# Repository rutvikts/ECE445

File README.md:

# ECE 445
UIUC ECE 445 - Senior Design Project Repository

# Project Details
## Oxygen Delivery Robot

Team Members:
- Rutvik Sayankar (rutviks2@illinois.edu)
- Aidan Dunican (dunican2@illinois.edu)
- Nazar Kalyniouk (nazark2@illinois.edu)

## Problem

Children's interstitial and diffuse lung disease (ChILD) is a collection of diseases or disorders. These diseases cause a thickening of the interstitium (the tissue that extends throughout the lungs) due to scarring, inflammation, or fluid buildup. This eventually affects a patient’s ability to breathe and distribute enough oxygen to the blood.

Numerous children experience the impact of this situation, requiring supplemental oxygen for their daily activities. It hampers the mobility and freedom of young infants, diminishing their growth and confidence. Moreover, parents face an increased burden, not only caring for their child but also being directly involved in managing the oxygen tank as their child moves around.

## Solution

Mobile oxygen delivery is a mostly untapped market for users both elderly and young. This project details a prototype design for a mobile oxygen delivery robot. We utilize a three-wheeled omnidirectional drivetrain, ultra-wideband triangulation, computer vision, and a simple Roomba-style bumper system. We remove ourselves from the context of dealing with oxygen-related tubing as swivel solutions already exist and focus on the issue of creating a robot that can autonomously and efficiently move an oxygen tank around in an indoor space.

### Final Robot Design

### Final Robot Wiring (Underside)

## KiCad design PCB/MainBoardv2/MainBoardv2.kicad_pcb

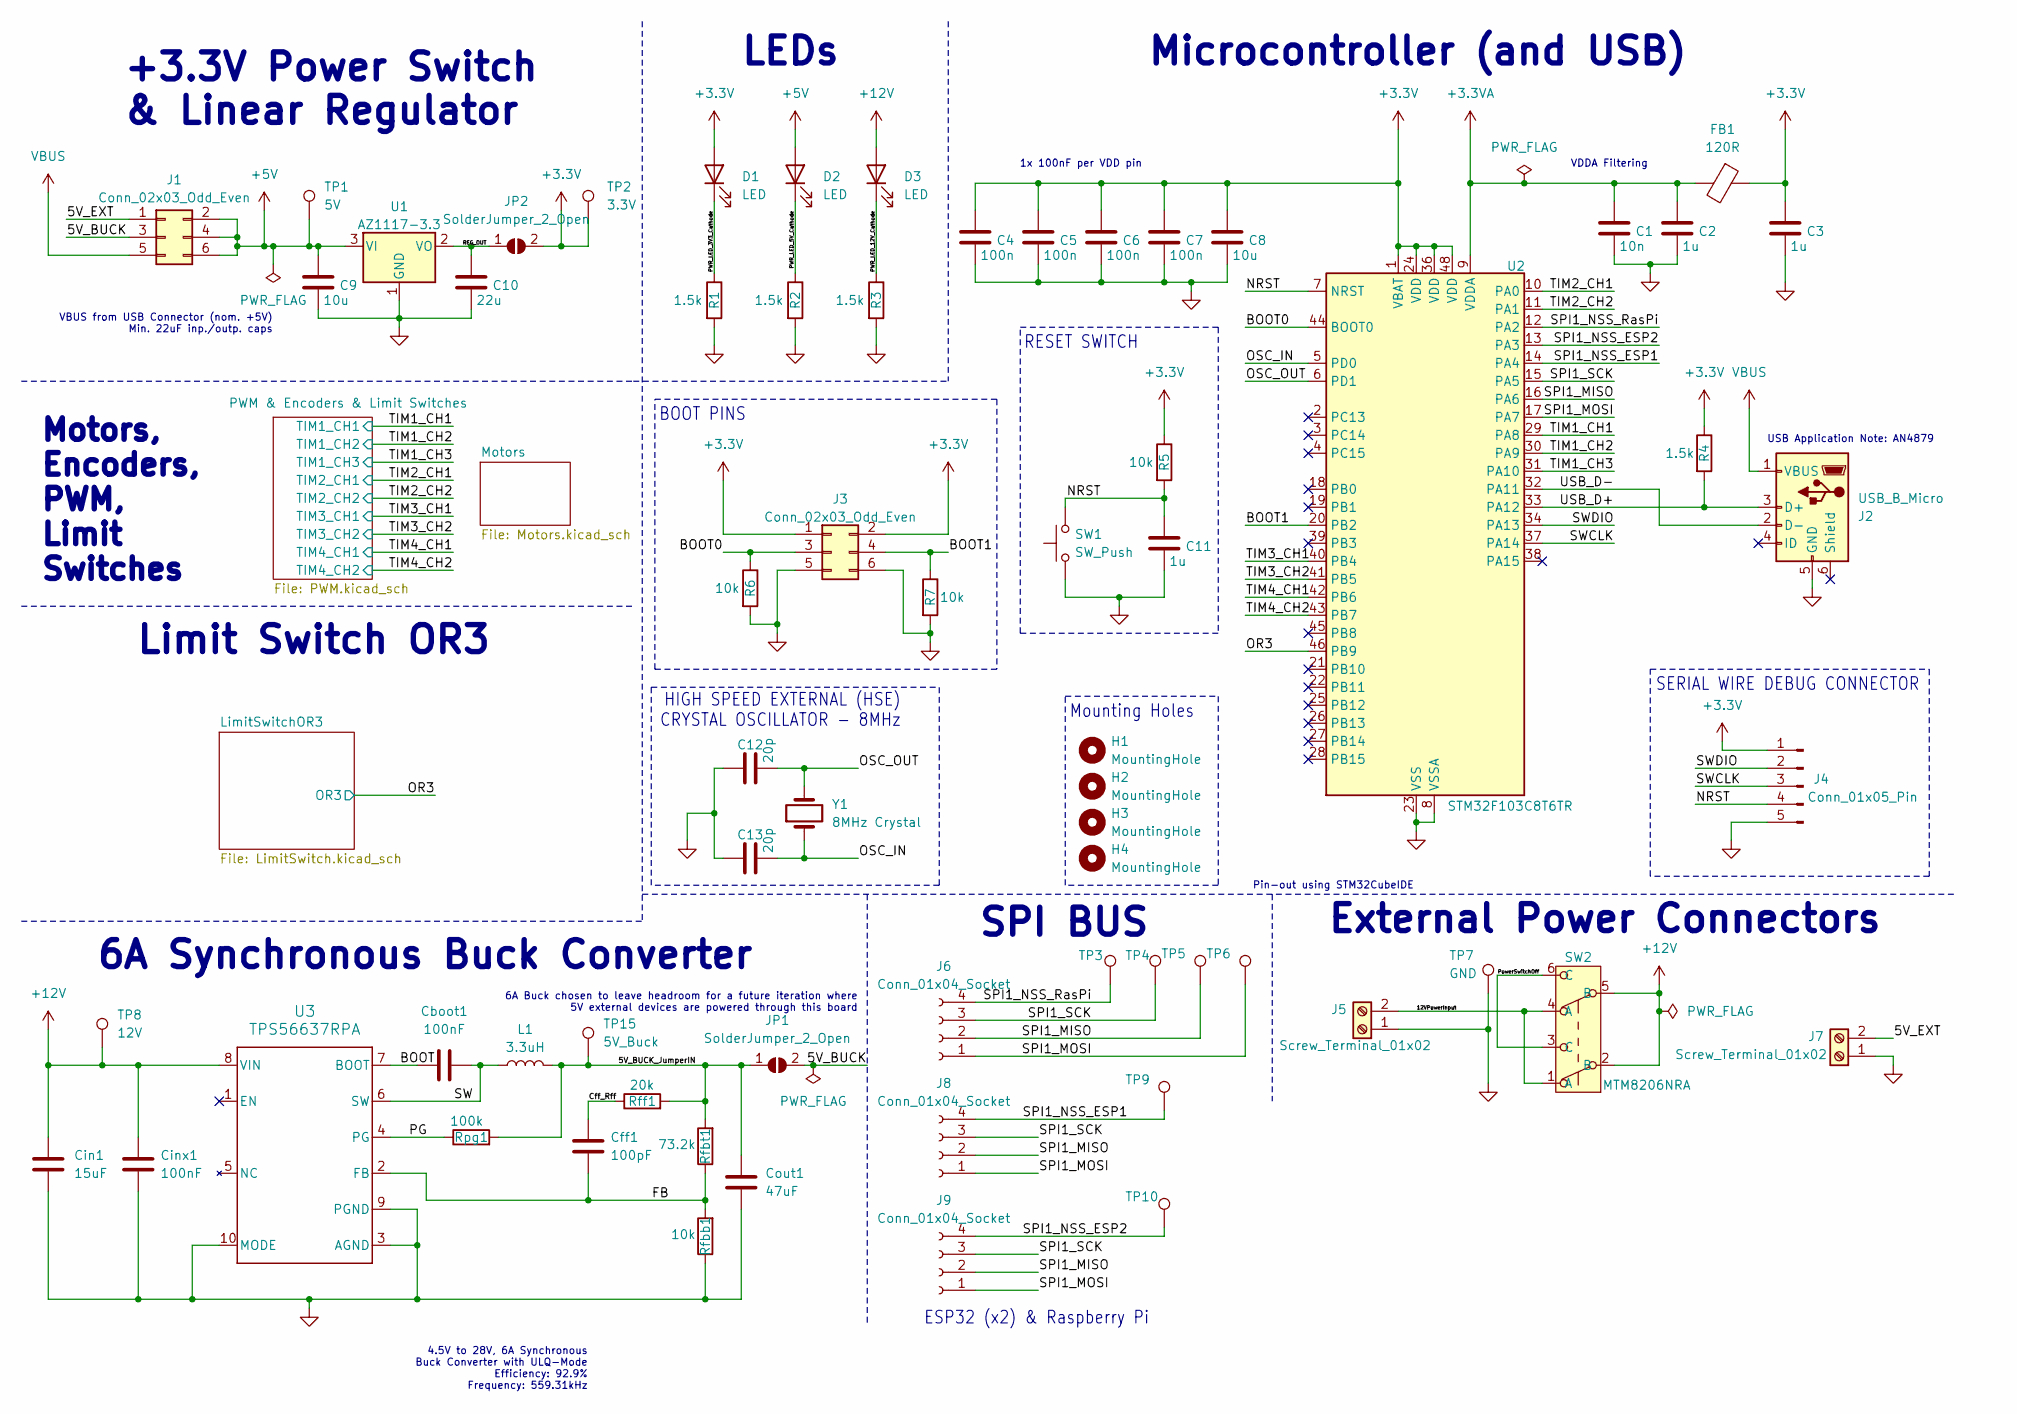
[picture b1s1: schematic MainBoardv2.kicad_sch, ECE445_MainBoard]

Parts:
C1: 10n; C_0603_1608Metric
C2, C3, C11: 1u; C_0603_1608Metric
C4, C5, C6, C7: 100n; C_0603_1608Metric
C8, C9: 10u; C_0603_1608Metric
C10: 22u; C_0805_2012Metric
C12, C13: 20p; C_0603_1608Metric
Cboot1: 100nF; C_0805_2012Metric
Cff1: 100pF; C_0805_2012Metric
Cin1: 15uF; C_0805_2012Metric
Cinx1: 100nF; C_0805_2012Metric
Cout1: 47uF; C_1210_3225Metric
D1, D2, D3: LED; LED_0603_1608Metric
FB1: 120R; L_0603_1608Metric
H1, H2, H3, H4: MountingHole; MountingHole_5mm
J1, J3: Conn_02x03_Odd_Even; PinHeader_2x03_P2.54mm_Vertical
J2: USB_B_Micro; AMPHENOL_10118192-0002LF
J4: Conn_01x05_Pin; PinSocket_1x05_P2.54mm_Vertical
J5, J7: Screw_Terminal_01x02; PHOENIX_1017521
J6, J8, J9: Conn_01x04_Socket; PinHeader_1x04_P2.54mm_Horizontal
JP1, JP2: SolderJumper_2_Open; SolderJumper-2_P1.3mm_Open_TrianglePad1.0x1.5mm
L1: 3.3uH; IHLP3232DZER3R3M01
R1, R2, R3, R4: 1.5k; R_0603_1608Metric
R5, R6, R7: 10k; R_0603_1608Metric
Rfbb1: 10k; R_0805_2012Metric
Rfbt1: 73.2k; R_0805_2012Metric
Rff1: 20k; R_0805_2012Metric
Rpg1: 100k; R_0805_2012Metric
SW1: SW_Push; SW_PUSH_6mm_H7.3mm
SW2: Toggle; MTM8206NRA
TP1: 5V; TestPoint_Keystone_5000-5004_Miniature
TP2: 3.3V; TestPoint_Keystone_5000-5004_Miniature
TP3, TP4, TP5, TP6, TP9, TP10: Orange; TestPoint_Keystone_5000-5004_Miniature
TP7: GND; TestPoint_Keystone_5000-5004_Miniature
TP8: 12V; TestPoint_Keystone_5000-5004_Miniature
TP15: 5V_Buck; TestPoint_Keystone_5000-5004_Miniature
U1: AZ1117-3.3; TO-252-2
U2: STM32F103C8T6TR; LQFP-48_7x7mm_P0.5mm
U3: TPS56637RPA; RPA0010A
Y1: 8MHz Crystal; Crystal_HC49-U_Vertical

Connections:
+3.3V: C3.1, C4.1, C5.1, C6.1, C7.1, C8.1, D1.2 (A), FB1.1, J3.1, J3.2, J4.1, JP2.2 (B), R4.1, R5.1, TP2.1, U2.1 (VBAT), U2.24 (VDD), U2.36 (VDD), U2.48 (VDD); also elsewhere on the board
+3.3VA: C1.1, C2.1, FB1.2, U2.9 (VDDA)
+5V: C9.1, D2.2 (A), J1.2, J1.4, J1.6, TP1.1, U1.3 (VI); also elsewhere on the board
+12V: Cin1.1, Cinx1.1, D3.2 (A), SW2.2 (B), SW2.5 (B), TP8.1, U3.8 (VIN); also elsewhere on the board
/5V_BUCK: J1.3, JP1.2 (B)
/5V_BUCK_JumperIN: Cout1.1, JP1.1 (A), L1.2, Rfbt1.2, Rff1.2, Rpg1.2, TP15.1
/5V_EXT: J1.1, J7.2
/12VPowerInput: J5.2, SW2.1 (A), SW2.4 (A)
/BOOT: Cboot1.1, U3.7 (BOOT)
/BOOT0: J3.3, R6.1, U2.44 (BOOT0)
/BOOT1: J3.4, R7.1, U2.20 (PB2)
/Cff_Rff: Cff1.1, Rff1.1
/FB: Cff1.2, Rfbb1.2, Rfbt1.1, U3.2 (FB)
/NRST: C11.1, J4.4, R5.2, SW1.2, U2.7 (NRST)
/OR3: U2.46 (PB9); also elsewhere on the board
/OSC_IN: C13.2, U2.5 (PD0), Y1.1
/OSC_OUT: C12.2, U2.6 (PD1), Y1.2
/PG: Rpg1.1, U3.4 (PG)
/PWR_LED_3V3_Cathode: D1.1 (K), R1.1
/PWR_LED_5V_Cathode: D2.1 (K), R2.1
/PWR_LED_12V_Cathode: D3.1 (K), R3.1
/PowerSwitchOff: SW2.3 (C), SW2.6 (C)
/REG_OUT: C10.1, JP2.1 (A), U1.2 (VO)
/SPI1_MISO: J6.2, J8.2, J9.2, TP5.1, U2.16 (PA6)
/SPI1_MOSI: J6.1, J8.1, J9.1, TP6.1, U2.17 (PA7)
/SPI1_NSS_ESP1: J8.4, TP9.1, U2.14 (PA4)
/SPI1_NSS_ESP2: J9.4, TP10.1, U2.13 (PA3)
/SPI1_NSS_RasPi: J6.4, TP3.1, U2.12 (PA2)
/SPI1_SCK: J6.3, J8.3, J9.3, TP4.1, U2.15 (PA5)
/SW: Cboot1.2, L1.1, U3.6 (SW)
/SWCLK: J4.3, U2.37 (PA14)
/SWDIO: J4.2, U2.34 (PA13)
/TIM1_CH1: U2.29 (PA8); also elsewhere on the board
/TIM1_CH2: U2.30 (PA9); also elsewhere on the board
/TIM1_CH3: U2.31 (PA10); also elsewhere on the board
/TIM2_CH1: U2.10 (PA0); also elsewhere on the board
/TIM2_CH2: U2.11 (PA1); also elsewhere on the board
/TIM3_CH1: U2.40 (PB4); also elsewhere on the board
/TIM3_CH2: U2.41 (PB5); also elsewhere on the board
/TIM4_CH1: U2.42 (PB6); also elsewhere on the board
/TIM4_CH2: U2.43 (PB7); also elsewhere on the board
/USB_D+: J2.3 (D+), R4.2, U2.33 (PA12)
/USB_D-: J2.2 (D-), U2.32 (PA11)
GND: C1.2, C2.2, C3.2, C4.2, C5.2, C6.2, C7.2, C8.2, C9.2, C10.2, C11.2, C12.1, C13.1, Cin1.2, Cinx1.2, Cout1.2, J2.5 (GND), J3.5, J3.6, J4.5, J5.1, J7.1, R1.2, R2.2, R3.2, R6.2, R7.2, Rfbb1.1, SW1.1, TP7.1, U1.1 (GND), U2.8 (VSSA), U2.23 (VSS), U2.35 (VSS), U2.47 (VSS), U3.3 (AGND), U3.9 (PGND), U3.10 (MODE); also elsewhere on the board
VBUS: J1.5, J2.1 (VBUS)

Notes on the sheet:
RESET SWITCH
Limit Switch OR3
SERIAL WIRE DEBUG CONNECTOR
BOOT PINS
VDDA Filtering
Microcontroller (and USB)
1x 100nF per VDD pin
External Power Connectors
LEDs
6A Buck chosen to leave headroom for a future iteration where 5V external devices are powered through this board
Pin-out using STM32CubeIDE
VBUS from USB Connector (nom. +5V) Min. 22uF inp./outp. caps
6A Synchronous Buck Converter
Motors, Encoders, PWM, Limit Switches
Mounting Holes
ESP32 (x2) & Raspberry Pi
USB Application Note: AN4879
4.5V to 28V, 6A Synchronous Buck Converter with ULQ-Mode Efficiency: 92.9% Frequency: 559.31kHz
SPI BUS
HIGH SPEED EXTERNAL (HSE) CRYSTAL OSCILLATOR - 8MHz
+3.3V Power Switch & Linear Regulator

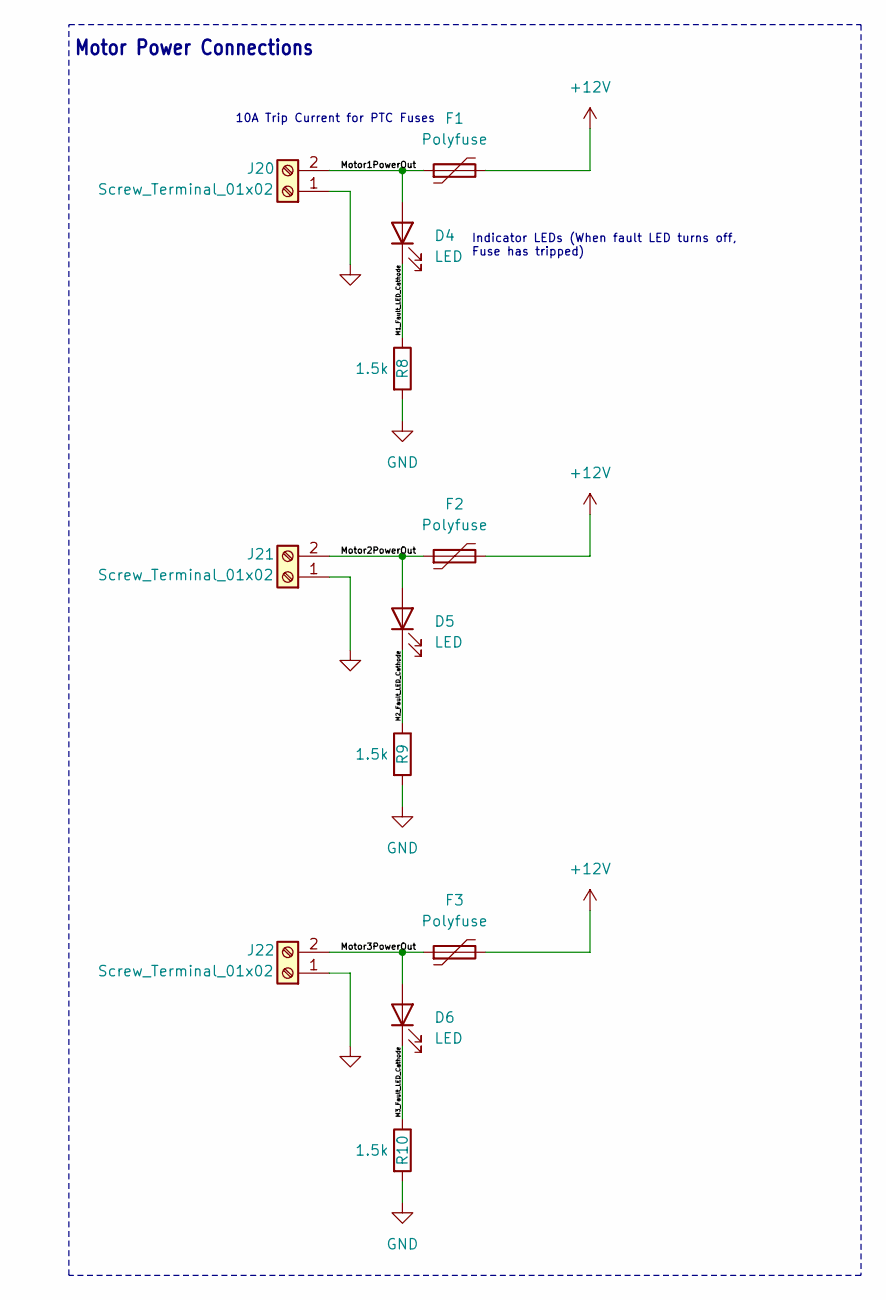
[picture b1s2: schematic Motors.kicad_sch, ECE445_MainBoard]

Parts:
D4, D5, D6: LED; LED_0603_1608Metric
F1, F2, F3: Polyfuse; Fuse_2920_7451Metric
J20, J21, J22: Screw_Terminal_01x02; PHOENIX_1017521
R8, R9, R10: 1.5k; R_0603_1608Metric

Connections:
+12V: F1.2, F2.2, F3.2; also elsewhere on the board
/Motors/M1_Fault_LED_Cathode: D4.1 (K), R8.1
/Motors/M2_Fault_LED_Cathode: D5.1 (K), R9.1
/Motors/M3_Fault_LED_Cathode: D6.1 (K), R10.1
/Motors/Motor1PowerOut: D4.2 (A), F1.1, J20.2
/Motors/Motor2PowerOut: D5.2 (A), F2.1, J21.2
/Motors/Motor3PowerOut: D6.2 (A), F3.1, J22.2
GND: J20.1, J21.1, J22.1, R8.2, R9.2, R10.2; also elsewhere on the board

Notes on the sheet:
Indicator LEDs (When fault LED turns off, Fuse has tripped)
Motor Power Connections
10A Trip Current for PTC Fuses

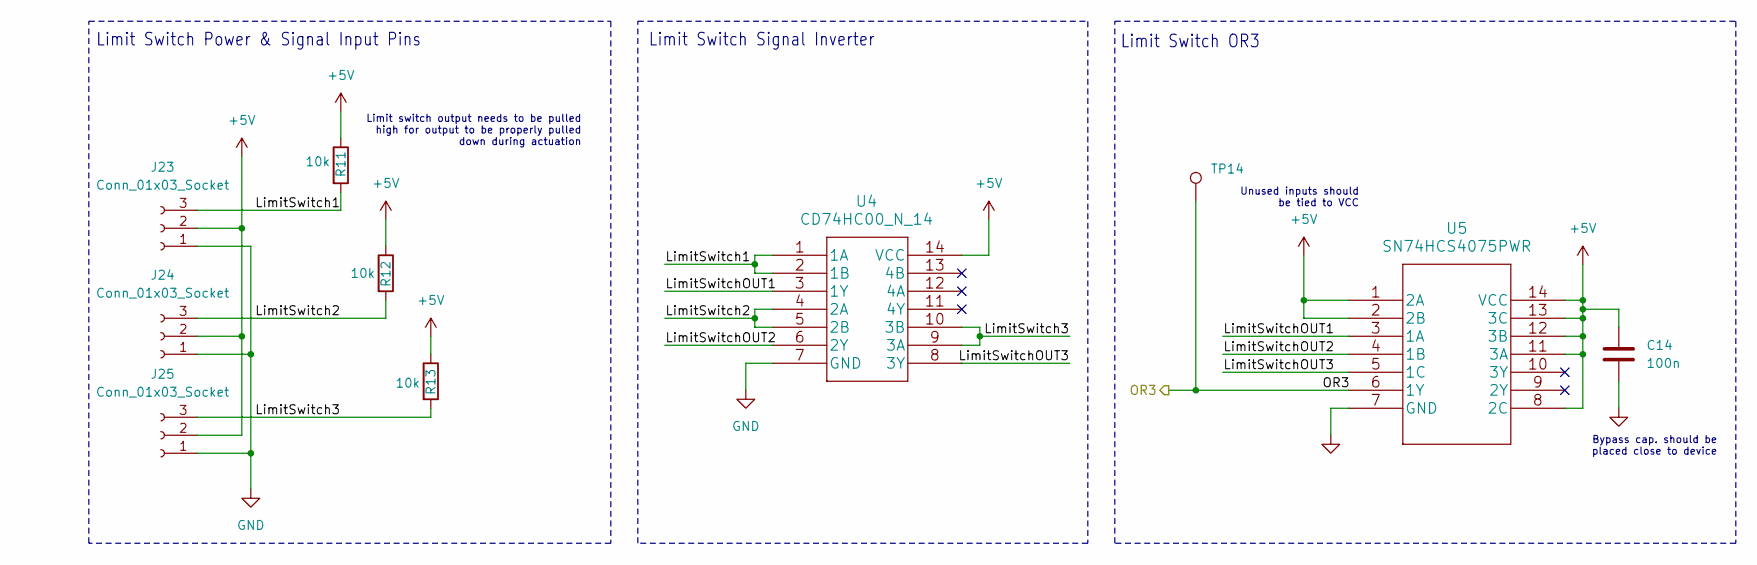
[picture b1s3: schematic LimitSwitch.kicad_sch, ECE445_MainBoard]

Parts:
C14: 100n; C_0603_1608Metric
J23, J24, J25: Conn_01x03_Socket; PinHeader_1x03_P2.54mm_Horizontal
R11, R12, R13: 10k; R_Axial_DIN0207_L6.3mm_D2.5mm_P7.62mm_Horizontal
TP14: White; TestPoint_Keystone_5000-5004_Miniature
U4: CD74HC00_N_14; DIP-14_W7.62mm_LongPads
U5: SN74HCS4075PWR

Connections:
+5V: C14.1, J23.2, J24.2, J25.2, R11.1, R12.1, R13.1, U4.14 (VCC), U5.1 (2A), U5.2 (2B), U5.8 (2C), U5.11 (3A), U5.12 (3B), U5.13 (3C), U5.14 (VCC); also elsewhere on the board
/LimitSwitchOR3/LimitSwitch1: J23.3, R11.2, U4.1 (1A), U4.2 (1B)
/LimitSwitchOR3/LimitSwitch2: J24.3, R12.2, U4.4 (2A), U4.5 (2B)
/LimitSwitchOR3/LimitSwitch3: J25.3, R13.2, U4.9 (3A), U4.10 (3B)
/LimitSwitchOR3/LimitSwitchOUT1: U4.3 (1Y), U5.3 (1A)
/LimitSwitchOR3/LimitSwitchOUT2: U4.6 (2Y), U5.4 (1B)
/LimitSwitchOR3/LimitSwitchOUT3: U4.8 (3Y), U5.5 (1C)
/OR3: TP14.1, U5.6 (1Y); also elsewhere on the board
GND: C14.2, J23.1, J24.1, J25.1, U4.7 (GND), U5.7 (GND); also elsewhere on the board

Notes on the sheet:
Bypass cap. should be placed close to device
Limit Switch OR3
Limit Switch Signal Inverter
Unused inputs should be tied to VCC
Limit switch output needs to be pulled high for output to be properly pulled down during actuation
Limit Switch Power & Signal Input Pins

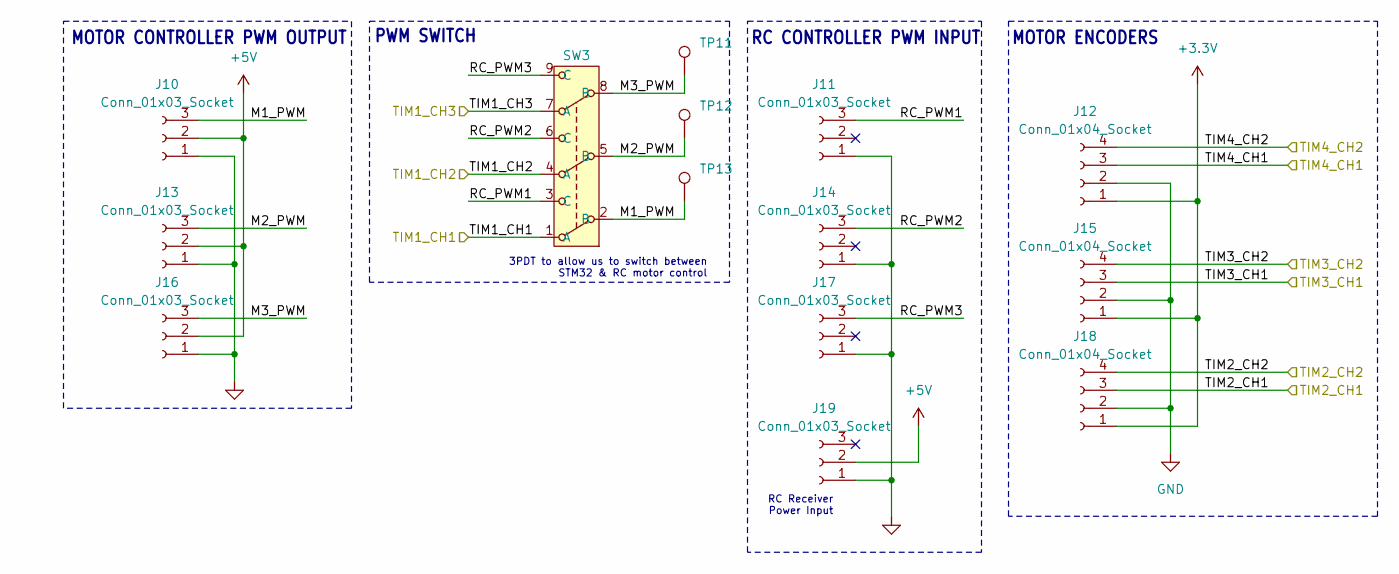
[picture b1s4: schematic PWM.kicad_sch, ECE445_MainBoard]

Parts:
J10, J13, J16: Conn_01x03_Socket; PinHeader_1x03_P2.54mm_Horizontal
J11, J14, J17, J19: Conn_01x03_Socket; PinHeader_1x03_P2.54mm_Vertical
J12, J15, J18: Conn_01x04_Socket; JST_PH_B4B-PH-K_1x04_P2.00mm_Vertical
SW3: Slide; SW_GF-161-0005
TP11, TP12, TP13: White; TestPoint_Keystone_5000-5004_Miniature

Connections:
+3.3V: J12.1, J15.1, J18.1; also elsewhere on the board
+5V: J10.2, J13.2, J16.2, J19.2; also elsewhere on the board
/PWM & Encoders & Limit Switches/M1_PWM: J10.3, SW3.2 (B), TP13.1
/PWM & Encoders & Limit Switches/M2_PWM: J13.3, SW3.5 (B), TP12.1
/PWM & Encoders & Limit Switches/M3_PWM: J16.3, SW3.8 (B), TP11.1
/PWM & Encoders & Limit Switches/RC_PWM1: J11.3, SW3.3 (C)
/PWM & Encoders & Limit Switches/RC_PWM2: J14.3, SW3.6 (C)
/PWM & Encoders & Limit Switches/RC_PWM3: J17.3, SW3.9 (C)
/TIM1_CH1: SW3.1 (A); also elsewhere on the board
/TIM1_CH2: SW3.4 (A); also elsewhere on the board
/TIM1_CH3: SW3.7 (A); also elsewhere on the board
/TIM2_CH1: J18.3; also elsewhere on the board
/TIM2_CH2: J18.4; also elsewhere on the board
/TIM3_CH1: J15.3; also elsewhere on the board
/TIM3_CH2: J15.4; also elsewhere on the board
/TIM4_CH1: J12.3; also elsewhere on the board
/TIM4_CH2: J12.4; also elsewhere on the board
GND: J10.1, J11.1, J12.2, J13.1, J14.1, J15.2, J16.1, J17.1, J18.2, J19.1; also elsewhere on the board

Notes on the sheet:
MOTOR ENCODERS
MOTOR CONTROLLER PWM OUTPUT
PWM SWITCH
RC Receiver Power Input
3PDT to allow us to switch between STM32 & RC motor control
RC CONTROLLER PWM INPUT

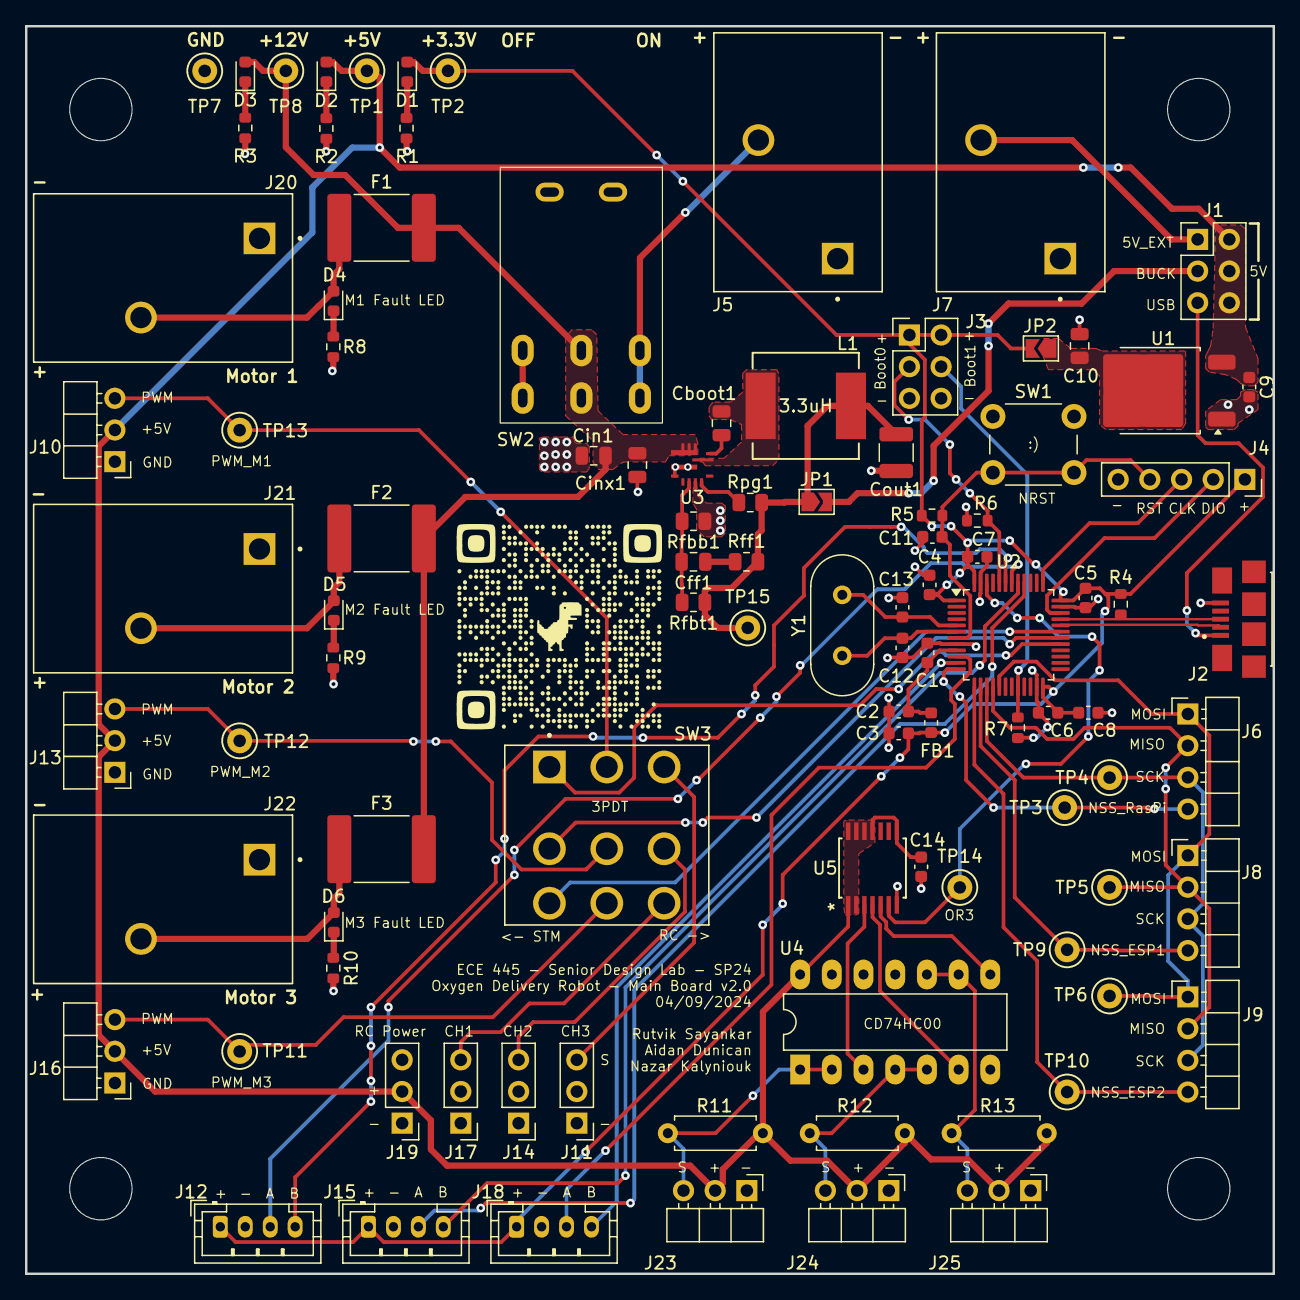
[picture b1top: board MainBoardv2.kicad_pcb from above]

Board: 2 copper layers, 100.0 x 100.0 mm, 102 parts (0 on the bottom side), 63 nets.

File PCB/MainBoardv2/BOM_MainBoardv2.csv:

Reference,Value,Datasheet,Footprint,Qty,DNP
C1,10n,https://www.digikey.com/en/products/detail/kemet/C0603C103K4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,Capacitor_SMD:C_0603_1608Metric,1,
"C2,C3,C11",1u,https://www.digikey.com/en/products/detail/yageo/CC0603KRX7R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,Capacitor_SMD:C_0603_1608Metric,3,
"C4,C5,C6,C7,C13",100n,https://www.digikey.com/en/products/detail/yageo/CC0603KRX7R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,Capacitor_SMD:C_0603_1608Metric,5,
"C8,C9",10u,https://www.digikey.com/en/products/detail/samsung-electro-m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,Capacitor_SMD:C_0603_1608Metric,2,
C10,22u,https://www.digikey.com/en/products/detail/samsung-electro-m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,Capacitor_SMD:C_0805_2012Metric,1,
"C12,C14",20p,https://www.digikey.com/en/products/detail/kemet/C0603C200G8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,Capacitor_SMD:C_0603_1608Metric,2,
Cboot?,100nF,https://www.digikey.com/en/products/detail/kyocera-avx/KGM21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,Capacitor_SMD:C_0805_2012Metric,1,
Cff?,100pF,https://www.digikey.com/en/products/detail/kemet/C0805C101K3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,Capacitor_SMD:C_0805_2012Metric,1,
Cin?,15uF,https://www.digikey.com/en/products/detail/tdk-corporation/C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,Capacitor_SMD:C_0805_2012Metric,1,
Cinx?,100nF,https://www.digikey.com/en/products/detail/knowles-syfer/080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,Capacitor_SMD:C_0805_2012Metric,1,
Cout?,47uF,https://www.digikey.com/en/products/detail/murata-electronic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,Capacitor_SMD:C_1210_3225Metric,1,
"D1,D2,D3,D4,D5,D6,D7,D8,D9",LED,https://www.digikey.com/en/products/detail/w%C3%BCrth-elektr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,LED_SMD:LED_0603_1608Metric,9,
"F1,F2,F3",Polyfuse,https://www.digikey.com/en/products/detail/yageo/SMD2920B500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,Fuse:Fuse_2920_7451Metric,3,
FB1,120R,https://www.digikey.com/en/products/detail/murata-electronic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,Inductor_SMD:L_0603_1608Metric,1,
"H1,H2,H3,H4",MountingHole,~,MountingHole:MountingHole_5mm,4,
"J1,J3",Conn_02x03_Odd_Even,~,Connector_PinSocket_2.54mm:PinSocket_2x03_P2.54mm_Vertical,2,
J2,USB_B_Micro,https://www.digikey.com/en/products/detail/amphenol-cs-fci/1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,CustomFootprints:AMPHENOL_10118192-0002LF,1,
J4,Conn_01x05_Pin,~,Connector_PinSocket_2.54mm:PinSocket_1x05_P2.54mm_Vertical,1,
"J5,J11,J12,J14,J15,J17,J18,J20",Conn_01x03_Socket,~,Connector_PinHeader_2.54mm:PinHeader_1x03_P2.54mm_Vertical,8,
"J6,J8,J21,J22,J23",Screw_Terminal_01x02,https://www.digikey.com/en/products/detail/phoenix-contact/1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,CustomFootprints:1985195,5,
"J7,J9,J10",Conn_01x04_Socket,~,Connector_PinHeader_2.54mm:PinHeader_1x04_P2.54mm_Vertical,3,
"J13,J16,J19",Conn_01x04_Socket,https://www.digikey.com/en/products/detail/jst-sales-america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,Connector_JST:JST_PH_B4B-PH-K_1x04_P2.00mm_Vertical,3,
L1,3.3uH,https://www.digikey.com/en/products/detail/vishay-dale/IHLP3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,CustomFootprints:IHLP3232DZER3R3M01,1,
"R1,R2,R3,R4,R8,R9,R10,R11,R12,R13",1.5k,https://www.digikey.com/en/products/detail/yageo/RC0603JR-07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,Resistor_SMD:R_0603_1608Metric,10,
"R5,R6,R7",10k,https://www.digikey.com/en/products/detail/stackpole-electro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,Resistor_SMD:R_0603_1608Metric,3,
Rfbb?,10k,https://www.digikey.com/en/products/detail/vishay-dale/CRCW0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,Resistor_SMD:R_0805_2012Metric,1,
Rfbt?,73.2k,https://www.digikey.com/en/products/detail/panasonic-electro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,Resistor_SMD:R_0805_2012Metric,1,
Rff?,20k,https://www.digikey.com/en/products/detail/vishay-dale/CRCW0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,Resistor_SMD:R_0805_2012Metric,1,
Rpg?,100k,https://www.digikey.com/en/products/detail/vishay-dale/CRCW0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,Resistor_SMD:R_0805_2012Metric,1,
SW1,SW_Push,https://www.digikey.com/en/products/detail/omron-electronics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,Button_Switch_SMD:SW_SPST_B3S-1000,1,
SW2,Toggle,https://mm.digikey.com/Volume0/opasdata/d220001/medias/docus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,CustomFootprints:MTM8206NRA,1,
SW3,Slide,https://www.digikey.com/en/products/detail/cw-industries/GF-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,CustomFootprints:SW_GF-161-0005,1,
TP1,5V,https://www.digikey.com/en/products/detail/keystone-electron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,TestPoint:TestPoint_Keystone_5000-5004_Miniature,1,
TP2,3.3V,https://www.digikey.com/en/products/detail/keystone-electron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,TestPoint:TestPoint_Keystone_5000-5004_Miniature,1,
"TP3,TP11,TP12,TP13",White,https://www.digikey.com/en/products/detail/keystone-electron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,TestPoint:TestPoint_Keystone_5000-5004_Miniature,4,
"TP4,TP5,TP6,TP7,TP9,TP10",Orange,https://www.digikey.com/en/products/detail/keystone-electron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,TestPoint:TestPoint_Keystone_5000-5004_Miniature,6,
TP8,12V,https://www.digikey.com/en/products/detail/keystone-electron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,TestPoint:TestPoint_Keystone_5000-5004_Miniature,1,
TP14,GND,https://www.digikey.com/en/products/detail/keystone-electron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,TestPoint:TestPoint_Keystone_5000-5004_Miniature,1,
U1,AZ1117-3.3,https://www.digikey.com/en/products/detail/diodes-incorporat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,Package_TO_SOT_SMD:TO-252-2,1,
U2,STM32F103C8T6TR,https://www.st.com/resource/en/datasheet/stm32f103c8.pdf,Package_QFP:LQFP-48_7x7mm_P0.5mm,1,
U3,SN74HCS4075PWR,https://www.digikey.com/en/products/detail/texas-instruments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,CustomFootprints:SN74HCS4075PWR,1,
U4,TPS56637RPA,https://www.digikey.com/en/products/detail/texas-instruments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,CustomFootprints:RPA0010A,1,
Y1,8MHz Crystal,https://www.digikey.com/en/products/detail/ecs-inc/ECS-080-2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,Crystal:Crystal_HC49-U_Vertical,1,

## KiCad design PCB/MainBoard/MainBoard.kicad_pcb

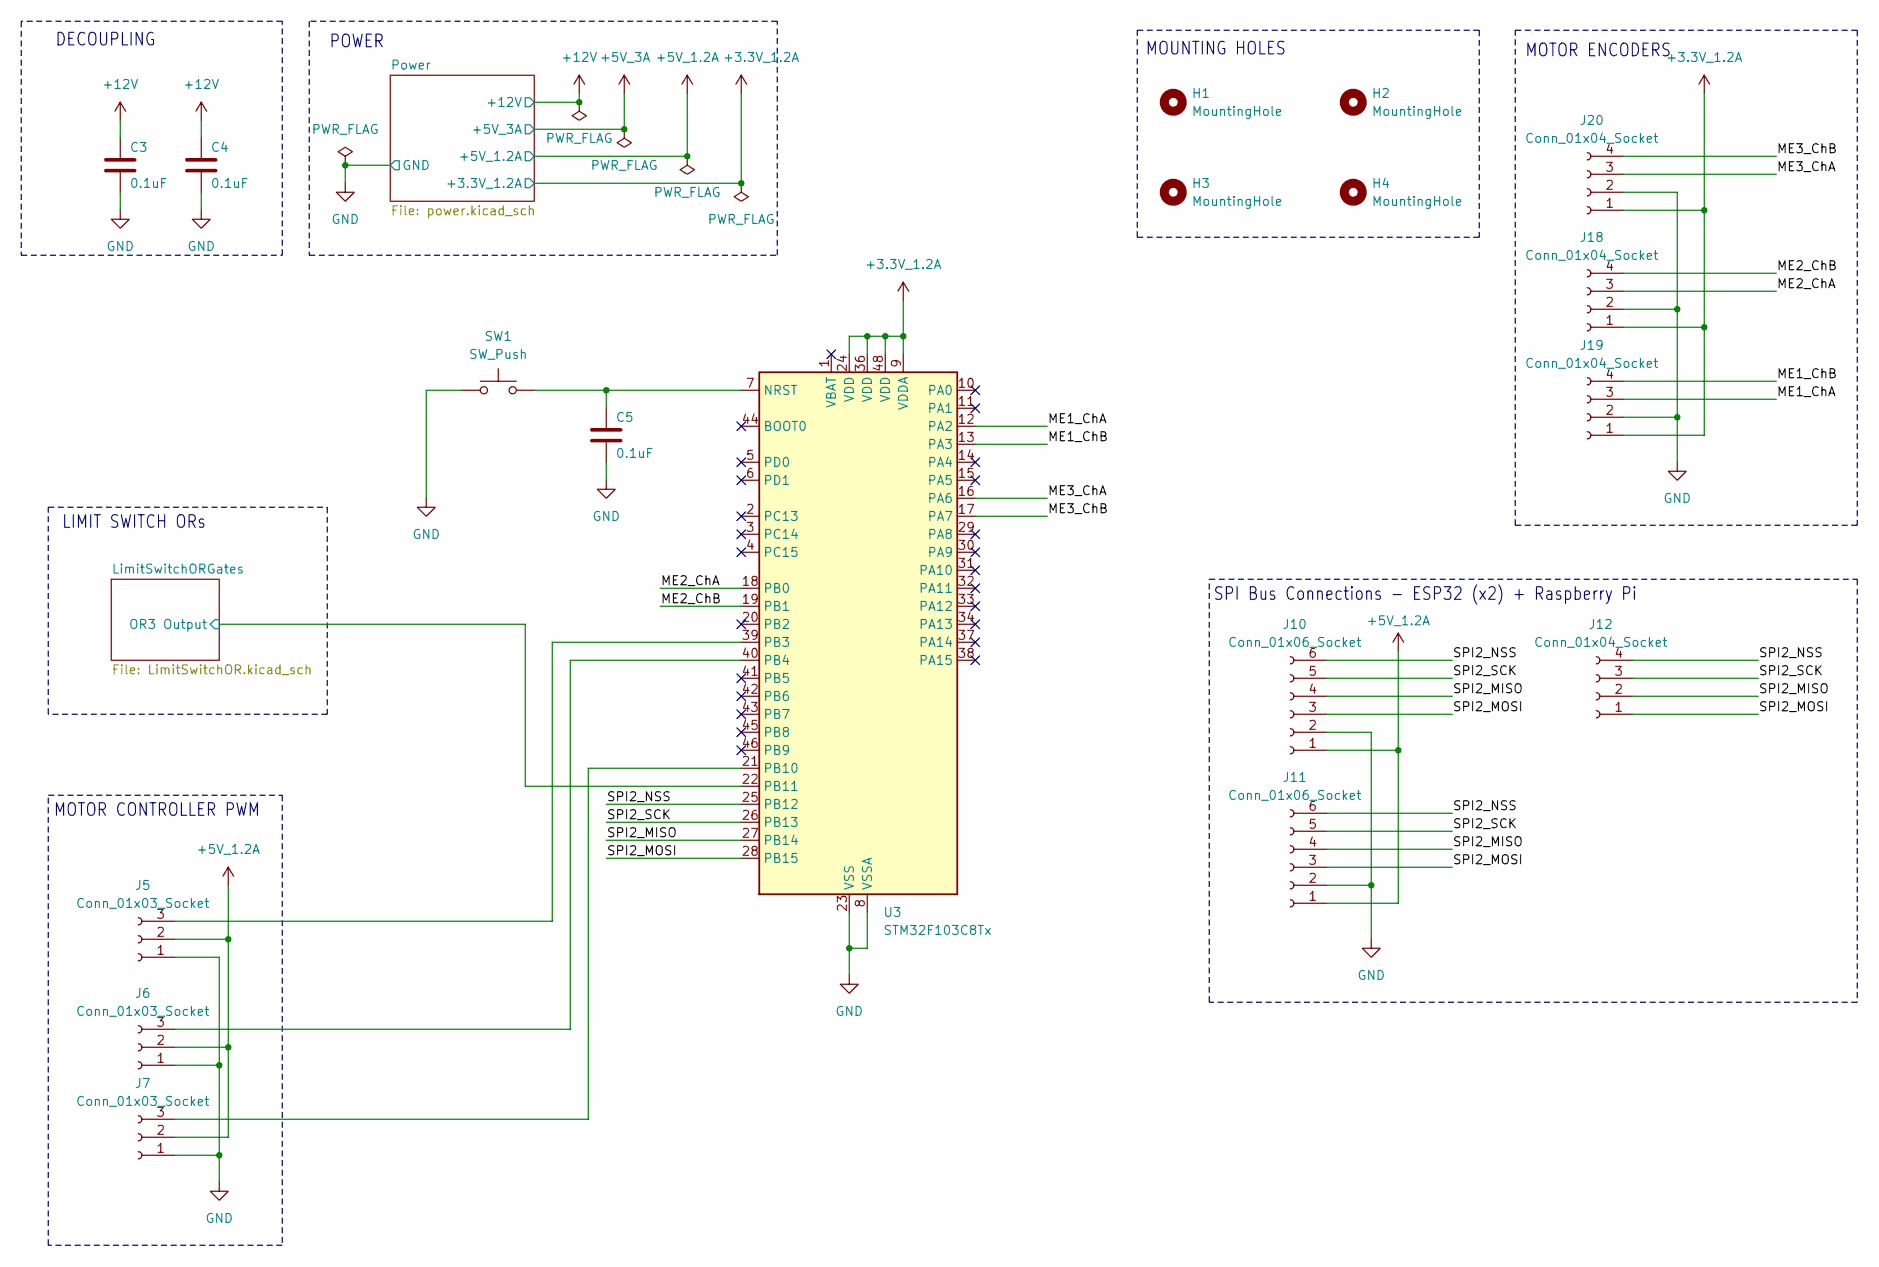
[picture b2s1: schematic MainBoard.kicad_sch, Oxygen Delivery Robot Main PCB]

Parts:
C3, C4, C5: 0.1uF; C_1206_3216Metric_Pad1.33x1.80mm_HandSolder
H1, H2, H3, H4: MountingHole; MountingHole_5mm
J5, J6, J7: Conn_01x03_Socket; PinHeader_1x03_P2.54mm_Vertical
J10, J11: Conn_01x06_Socket; PinHeader_1x06_P2.54mm_Vertical
J12: Conn_01x04_Socket; PinHeader_1x04_P2.54mm_Vertical
J18, J19, J20: Conn_01x04_Socket; JST_XH_B4B-XH-A_1x04_P2.50mm_Vertical
SW1: SW_Push; SW_PUSH_6mm_H7.3mm
U3: STM32F103C8Tx; LQFP-48_7x7mm_P0.5mm

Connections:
+3.3V_1.2A: J18.1, J19.1, J20.1, U3.9 (VDDA), U3.24 (VDD), U3.36 (VDD), U3.48 (VDD); also elsewhere on the board
+5V_1.2A: J5.2, J6.2, J7.2, J10.1, J11.1; also elsewhere on the board
+12V: C3.1, C4.1; also elsewhere on the board
/LimitSwitchORGates/OR3 Output: U3.22 (PB11); also elsewhere on the board
/ME1_ChA: J19.3, U3.12 (PA2)
/ME1_ChB: J19.4, U3.13 (PA3)
/ME2_ChA: J18.3, U3.18 (PB0)
/ME2_ChB: J18.4, U3.19 (PB1)
/ME3_ChA: J20.3, U3.16 (PA6)
/ME3_ChB: J20.4, U3.17 (PA7)
/SPI2_MISO: J10.4, J11.4, J12.2, U3.27 (PB14)
/SPI2_MOSI: J10.3, J11.3, J12.1, U3.28 (PB15)
/SPI2_NSS: J10.6, J11.6, J12.4, U3.25 (PB12)
/SPI2_SCK: J10.5, J11.5, J12.3, U3.26 (PB13)
GND: C3.2, C4.2, C5.2, J5.1, J6.1, J7.1, J10.2, J11.2, J18.2, J19.2, J20.2, SW1.1, U3.8 (VSSA), U3.23 (VSS), U3.35 (VSS), U3.47 (VSS); also elsewhere on the board
unnamed: J5.3, U3.39 (PB3)
unnamed: J6.3, U3.40 (PB4)
unnamed: J7.3, U3.21 (PB10)
unnamed: C5.1, SW1.2, U3.7 (NRST)

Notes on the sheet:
POWER
DECOUPLING
SPI Bus Connections - ESP32 (x2) + Raspberry Pi
MOUNTING HOLES
LIMIT SWITCH ORs
MOTOR ENCODERS
MOTOR CONTROLLER PWM

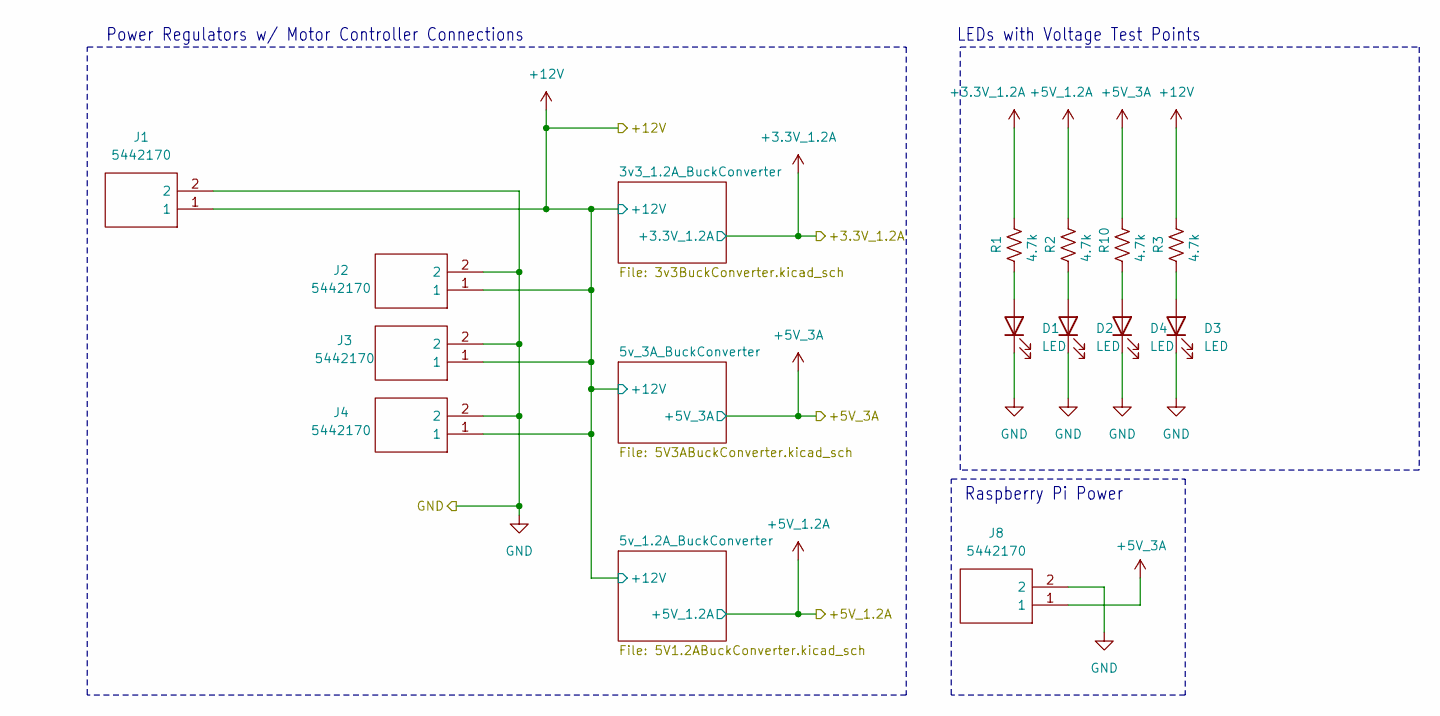
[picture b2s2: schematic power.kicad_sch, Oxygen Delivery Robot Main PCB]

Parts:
D1, D2, D3, D4: LED; LED_D3.0mm_Clear
J1, J2, J3, J4, J8: 5442170; Mouser Part Number 651-5442170
R1, R2, R3, R10: 4.7k; R_Axial_DIN0207_L6.3mm_D2.5mm_P7.62mm_Horizontal

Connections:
+3.3V_1.2A: R1.1; also elsewhere on the board
+5V_1.2A: R2.1; also elsewhere on the board
+5V_3A: J8.1, R10.1; also elsewhere on the board
+12V: J1.1, J2.1, J3.1, J4.1, R3.1; also elsewhere on the board
GND: D1.1 (K), D2.1 (K), D3.1 (K), D4.1 (K), J1.2, J2.2, J3.2, J4.2, J8.2; also elsewhere on the board
unnamed: D1.2 (A), R1.2
unnamed: D2.2 (A), R2.2
unnamed: D3.2 (A), R3.2
unnamed: D4.2 (A), R10.2

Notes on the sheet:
Power Regulators w/ Motor Controller Connections
Raspberry Pi Power
LEDs with Voltage Test Points

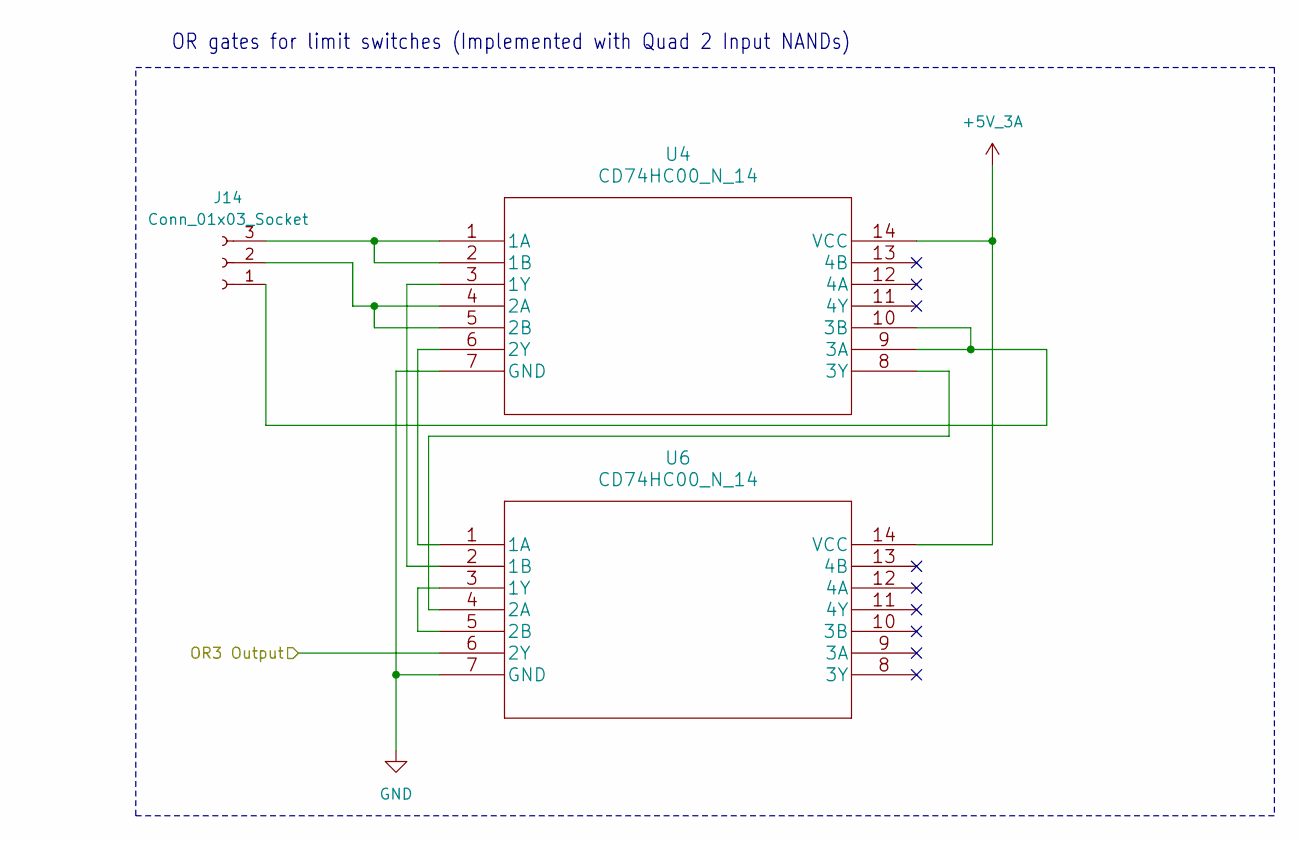
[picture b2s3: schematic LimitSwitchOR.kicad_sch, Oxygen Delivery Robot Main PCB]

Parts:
J14: Conn_01x03_Socket; PinHeader_1x03_P2.54mm_Vertical
U4, U6: CD74HC00_N_14; DIP-14_W7.62mm_LongPads

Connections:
+5V_3A: U4.14 (VCC), U6.14 (VCC); also elsewhere on the board
/LimitSwitchORGates/OR3 Output: U6.6 (2Y); also elsewhere on the board
GND: U4.7 (GND), U6.7 (GND); also elsewhere on the board
unnamed: J14.1, U4.9 (3A), U4.10 (3B)
unnamed: J14.2, U4.4 (2A), U4.5 (2B)
unnamed: J14.3, U4.1 (1A), U4.2 (1B)
unnamed: U4.3 (1Y), U6.2 (1B)
unnamed: U4.6 (2Y), U6.1 (1A)
unnamed: U4.8 (3Y), U6.4 (2A)
unnamed: U6.3 (1Y), U6.5 (2B)

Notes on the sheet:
OR gates for limit switches (Implemented with Quad 2 Input NANDs)

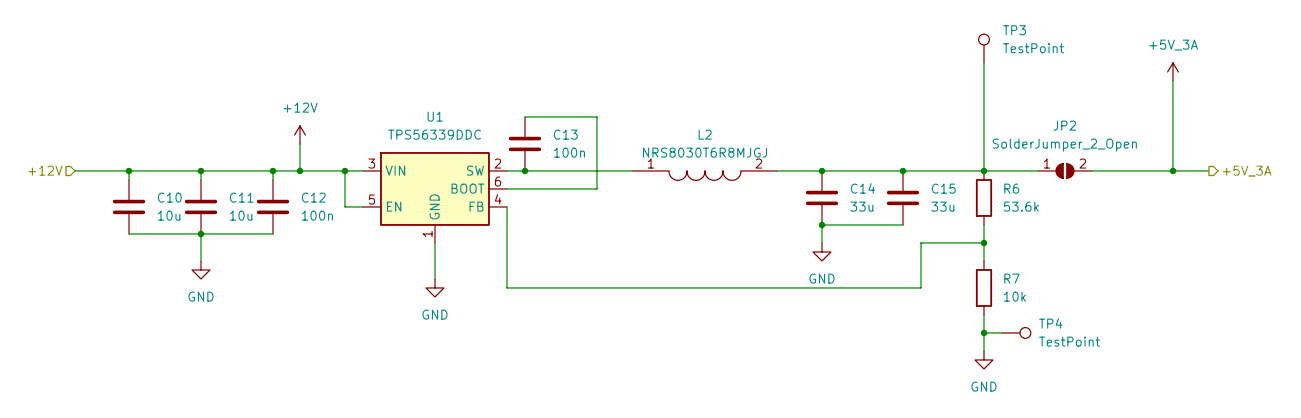
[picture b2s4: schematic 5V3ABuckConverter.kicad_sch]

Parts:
C10, C11: 10u; C_1206_3216Metric_Pad1.33x1.80mm_HandSolder
C12, C13: 100n; C_1206_3216Metric_Pad1.33x1.80mm_HandSolder
C14, C15: 33u; C_1206_3216Metric_Pad1.33x1.80mm_HandSolder
JP2: SolderJumper_2_Open; SolderJumper-2_P1.3mm_Open_TrianglePad1.0x1.5mm
L2: NRS8030T6R8MJGJ; Mouser Part Number 963-NRS8030T6R8MJGJ
R6: 53.6k; R_Axial_DIN0207_L6.3mm_D2.5mm_P7.62mm_Horizontal
R7: 10k; R_Axial_DIN0207_L6.3mm_D2.5mm_P7.62mm_Horizontal
TP3, TP4: TestPoint; PinHeader_1x01_P2.54mm_Vertical
U1: TPS56339DDC; SOT-23-6

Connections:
+5V_3A: JP2.2 (B); also elsewhere on the board
+12V: C10.1, C11.1, C12.1, U1.3 (VIN), U1.5 (EN); also elsewhere on the board
GND: C10.2, C11.2, C12.2, C14.2, C15.2, R7.2, TP4.1, U1.1 (GND); also elsewhere on the board
unnamed: C14.1, C15.1, JP2.1 (A), L2.2, R6.1, TP3.1
unnamed: C13.1, U1.6 (BOOT)
unnamed: R6.2, R7.1, U1.4 (FB)
unnamed: C13.2, L2.1, U1.2 (SW)

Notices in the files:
STM32/OxygenDeliveryRobotFirmware/Core/Src/stm32f1xx_hal_msp.c:
Copyright (c) 2024 STMicroelectronics.
All rights reserved.
This software is licensed under terms that can be found in the LICENSE file
